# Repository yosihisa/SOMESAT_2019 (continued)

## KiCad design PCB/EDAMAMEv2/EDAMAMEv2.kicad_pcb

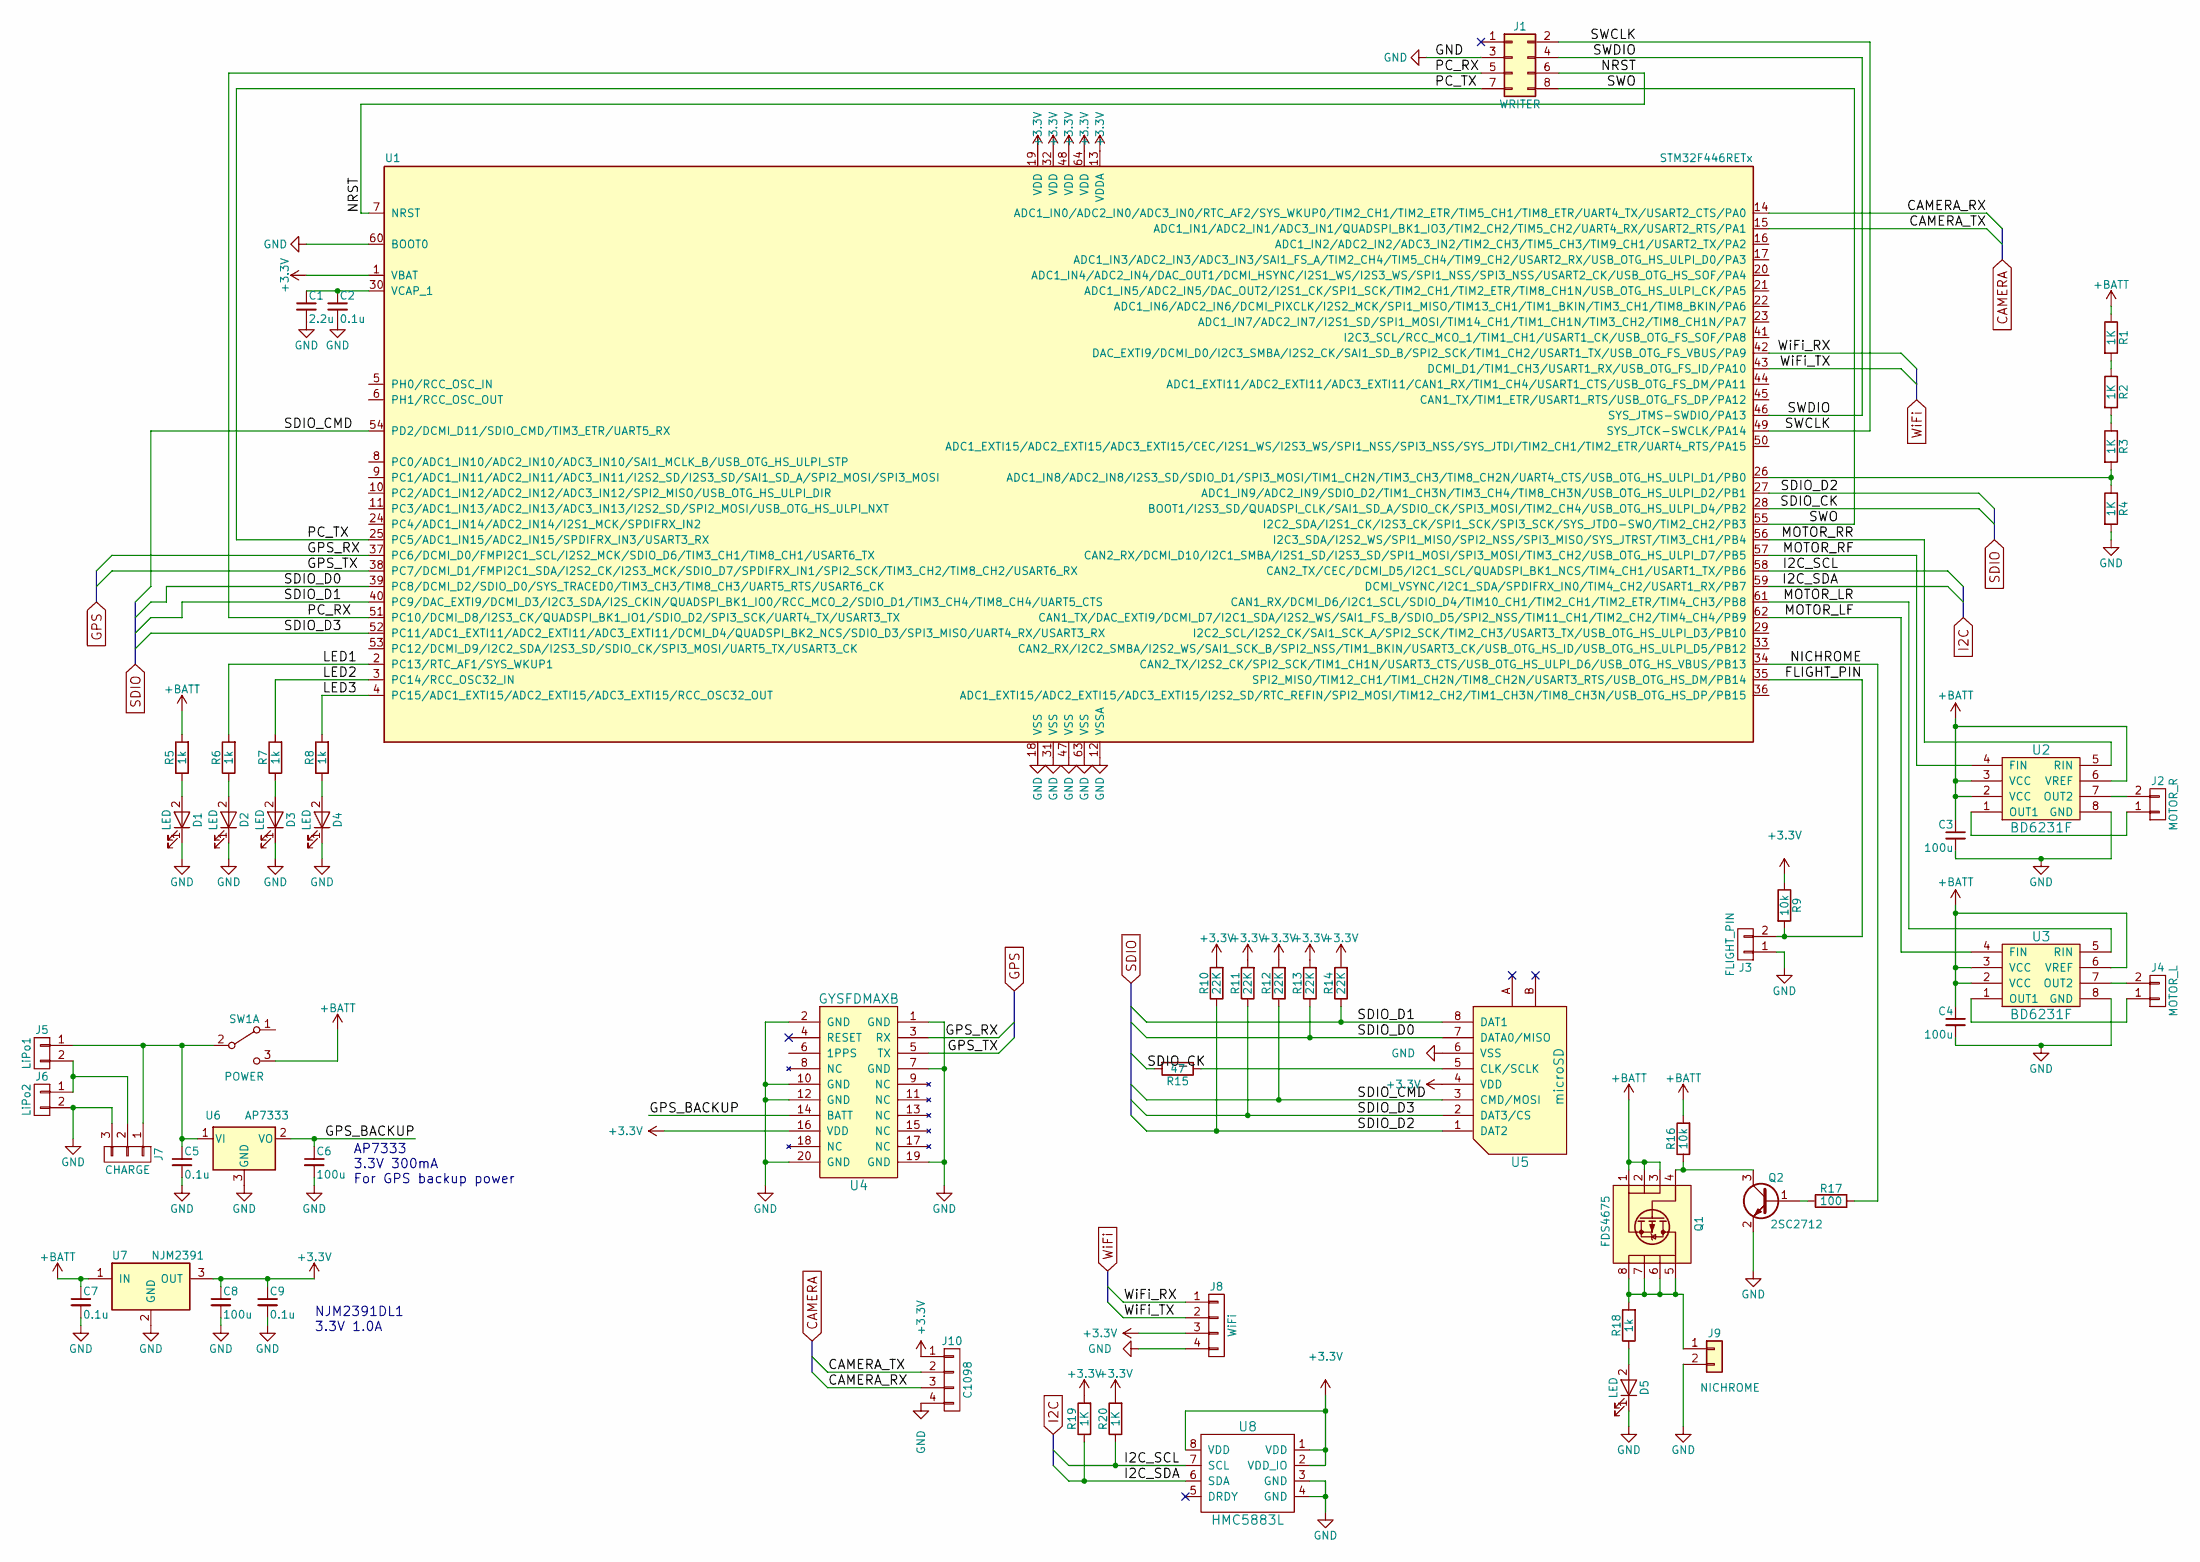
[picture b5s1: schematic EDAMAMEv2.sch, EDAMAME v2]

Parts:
C1: 2.2u; C_0603_HandSoldering
C2, C5, C7, C9: 0.1u; C_0603_HandSoldering
C3, C4: 100u; C_1210_HandSoldering
C6, C8: 100u; C_1206_HandSoldering
D1, D2, D3, D4, D5: LED; LED_0603
J1: WRITER; Pin_Header_Straight_2x04_Pitch2.54mm
J2: MOTOR_R; B2B-EH
J3: FLIGHT_PIN; Pin_Header_Angled_1x02_Pitch2.54mm
J4: MOTOR_L; B2B-EH
J5: LiPo1; S2B-EH
J6: LiPo2; S2B-EH
J7: CHARGE; B3B-EH
J8: WiFi; ZUNDA_WIRELESS
J9: NICHROME; TerminalBlock_bornier-2_P5.08mm
J10: C1098; Pin_Header_Straight_1x04_Pitch2.00mm
Q1: FDS4675; SOIC-8_3.9x4.9mm_Pitch1.27mm
Q2: 2SC2712; SOT-23_Handsoldering
R1, R2, R3, R4, R19, R20: 1K; R_0603_HandSoldering
R5, R6, R7, R8, R18: 1k; R_0603_HandSoldering
R9, R16: 10k; R_0603_HandSoldering
R10, R11, R12, R13, R14: 22K; R_0603_HandSoldering
R15: 47; R_0603_HandSoldering
R17: 100; R_0603_HandSoldering
SW1: POWER; SS-12D01-VG4
U1: STM32F446RETx; LQFP-64_10x10mm_Pitch0.5mm
U2, U3: BD6231F; SOIC-8_3.9x4.9mm_Pitch1.27mm
U4: GYSFDMAXB
U5: microSD
U6: AP7333; SOT-23
U7: NJM2391; TO-252-2_Rectifier
U8: HMC5883L; DIP-8_W7.62mm

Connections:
+3V3: C8.1, C9.1, J8.3, J10.1, R9.1, R10.2, R11.2, R12.2, R13.2, R14.2, R19.2, R20.2, U1.1 (VBAT), U1.13 (VDDA), U1.19 (VDD), U1.32 (VDD), U1.48 (VDD), U1.64 (VDD), U4.16 (VDD), U5.4 (VDD), U7.3 (OUT), U8.1 (VDD), U8.2 (VDD_IO), U8.8 (VDD)
+BATT: C3.1, C4.1, C7.1, Q1.1 (D), Q1.2 (G), Q1.3 (S), R1.1, R5.2, R16.2, SW1.3 (C), U2.2 (VCC), U2.3 (VCC), U2.6 (VREF), U3.2 (VCC), U3.3 (VCC), U3.6 (VREF), U7.1 (IN)
/CAMERA_RX: J10.3, U1.14 (ADC1_IN0/ADC2_IN0/ADC3_IN0/RTC_AF2/SYS_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)
/CAMERA_TX: J10.2, U1.15 (ADC1_IN1/ADC2_IN1/ADC3_IN1/QUADSPI_BK1_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)
/FLIGHT_PIN: J3.2, R9.2, U1.35 (SPI2_MISO/TIM12_CH1/TIM1_CH2N/TIM8_CH2N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)
/GPS_BACKUP: C6.1, U4.14 (BATT), U6.2 (VO)
/GPS_RX: U1.37 (PC6/DCMI_D0/FMPI2C1_SCL/I2S2_MCK/SDIO_D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), U4.3 (RX)
/GPS_TX: U1.38 (PC7/DCMI_D1/FMPI2C1_SDA/I2S2_CK/I2S3_MC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), U4.5 (TX)
/I2C_SCL: R20.1, U1.58 (CAN2_TX/CEC/DCMI_D5/I2C1_SCL/QUADSPI_BK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), U8.7 (SCL)
/I2C_SDA: R19.1, U1.59 (DCMI_VSYNC/I2C1_SDA/SPDIFRX_IN0/TIM4_CH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), U8.6 (SDA)
/LED1: R6.2, U1.2 (PC13/RTC_AF1/SYS_WKUP1)
/LED2: R7.2, U1.3 (PC14/RCC_OSC32_IN)
/LED3: R8.2, U1.4 (PC15/ADC1_EXTI15/ADC2_EXTI15/ADC3_EXTI1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)
/MOTOR_LF: U1.62 (CAN1_TX/DAC_EXTI9/DCMI_D7/I2C1_SDA/I2S2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), U3.4 (FIN)
/MOTOR_LR: U1.61 (CAN1_RX/DCMI_D6/I2C1_SCL/SDIO_D4/TIM10_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), U3.5 (RIN)
/MOTOR_RF: U1.57 (CAN2_RX/DCMI_D10/I2C1_SMBA/I2S1_SD/I2S3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), U2.4 (FIN)
/MOTOR_RR: U1.56 (I2C3_SDA/I2S2_WS/SPI1_MISO/SPI2_NSS/SPI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), U2.5 (RIN)
/NICHROME: R17.2, U1.34 (CAN2_TX/I2S2_CK/SPI2_SCK/TIM1_CH1N/USAR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)
/NRST: J1.6, U1.7 (NRST)
/PC_RX: J1.5, U1.51 (PC10/DCMI_D8/I2S3_CK/QUADSPI_BK1_IO1/SD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)
/PC_TX: J1.7, U1.25 (PC5/ADC1_IN15/ADC2_IN15/SPDIFRX_IN3/USA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)
/SDIO_CK: R15.2, U1.28 (BOOT1/I2S3_SD/QUADSPI_CLK/SAI1_SD_A/SDI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)
/SDIO_CMD: R12.1, U1.54 (PD2/DCMI_D11/SDIO_CMD/TIM3_ETR/UART5_RX), U5.3 (CMD/MOSI)
/SDIO_D0: R13.1, U1.39 (PC8/DCMI_D2/SDIO_D0/SYS_TRACED0/TIM3_CH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), U5.7 (DATA0/MISO)
/SDIO_D1: R14.1, U1.40 (PC9/DAC_EXTI9/DCMI_D3/I2C3_SDA/I2S_CKIN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), U5.8 (DAT1)
/SDIO_D2: R10.1, U1.27 (ADC1_IN9/ADC2_IN9/SDIO_D2/TIM1_CH3N/TIM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), U5.1 (DAT2)
/SDIO_D3: R11.1, U1.52 (PC11/ADC1_EXTI11/ADC2_EXTI11/ADC3_EXTI1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), U5.2 (DAT3/CS)
/SWCLK: J1.2, U1.49 (SYS_JTCK-SWCLK/PA14)
/SWDIO: J1.4, U1.46 (SYS_JTMS-SWDIO/PA13)
/SWO: J1.8, U1.55 (I2C2_SDA/I2S1_CK/I2S3_CK/SPI1_SCK/SPI3_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)
/WiFi_RX: J8.1, U1.42 (DAC_EXTI9/DCMI_D0/I2C3_SMBA/I2S2_CK/SAI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)
/WiFi_TX: J8.2, U1.43 (DCMI_D1/TIM1_CH3/USART1_RX/USB_OTG_FS_I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)
GND: C1.2, C2.2, C3.2, C4.2, C5.2, C6.2, C7.2, C8.2, C9.2, D1.1 (K), D2.1 (K), D3.1 (K), D4.1 (K), D5.1 (K), J1.3, J3.1, J6.2, J7.3, J8.4, J9.2, J10.4, Q2.2 (E), R4.2, U1.12 (VSSA), U1.18 (VSS), U1.31 (VSS), U1.47 (VSS), U1.60 (BOOT0), U1.63 (VSS), U2.8 (GND), U3.8 (GND), U4.1 (GND), U4.2 (GND), U4.7 (GND), U4.10 (GND), U4.12 (GND), U4.19 (GND), U4.20 (GND), U5.6 (VSS), U6.3 (GND), U7.2 (GND), U8.3 (GND), U8.4 (GND)
unnamed: C1.1, C2.1, U1.30 (VCAP_1)
unnamed: C5.1, J5.1, J7.1, SW1.2 (B), U6.1 (VI)
unnamed: D1.2 (A), R5.1
unnamed: D2.2 (A), R6.1
unnamed: D3.2 (A), R7.1
unnamed: D4.2 (A), R8.1
unnamed: D5.2 (A), R18.1
unnamed: J2.1, U2.1 (OUT1)
unnamed: J2.2, U2.7 (OUT2)
unnamed: J4.1, U3.1 (OUT1)
unnamed: J4.2, U3.7 (OUT2)
unnamed: J5.2, J6.1, J7.2
unnamed: J9.1, Q1.5, Q1.6, Q1.7, Q1.8, R18.2
unnamed: Q1.4, Q2.3 (C), R16.1
unnamed: Q2.1 (B), R17.1
unnamed: R1.2, R2.1
unnamed: R2.2, R3.1
unnamed: R3.2, R4.1, U1.26 (ADC1_IN8/ADC2_IN8/I2S3_SD/SDIO_D1/SPI3_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)
unnamed: R15.1, U5.5 (CLK/SCLK)

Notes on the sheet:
NJM2391DL1 3.3V 1.0A
AP7333 3.3V 300mA For GPS backup power

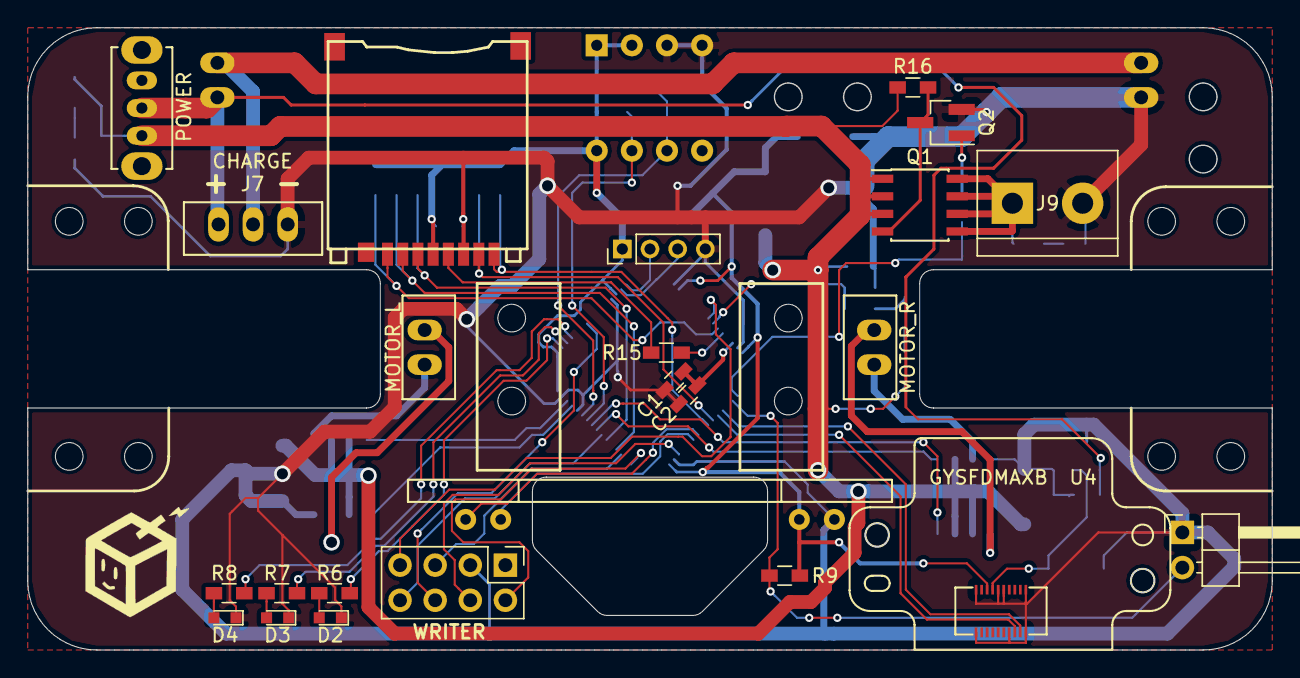
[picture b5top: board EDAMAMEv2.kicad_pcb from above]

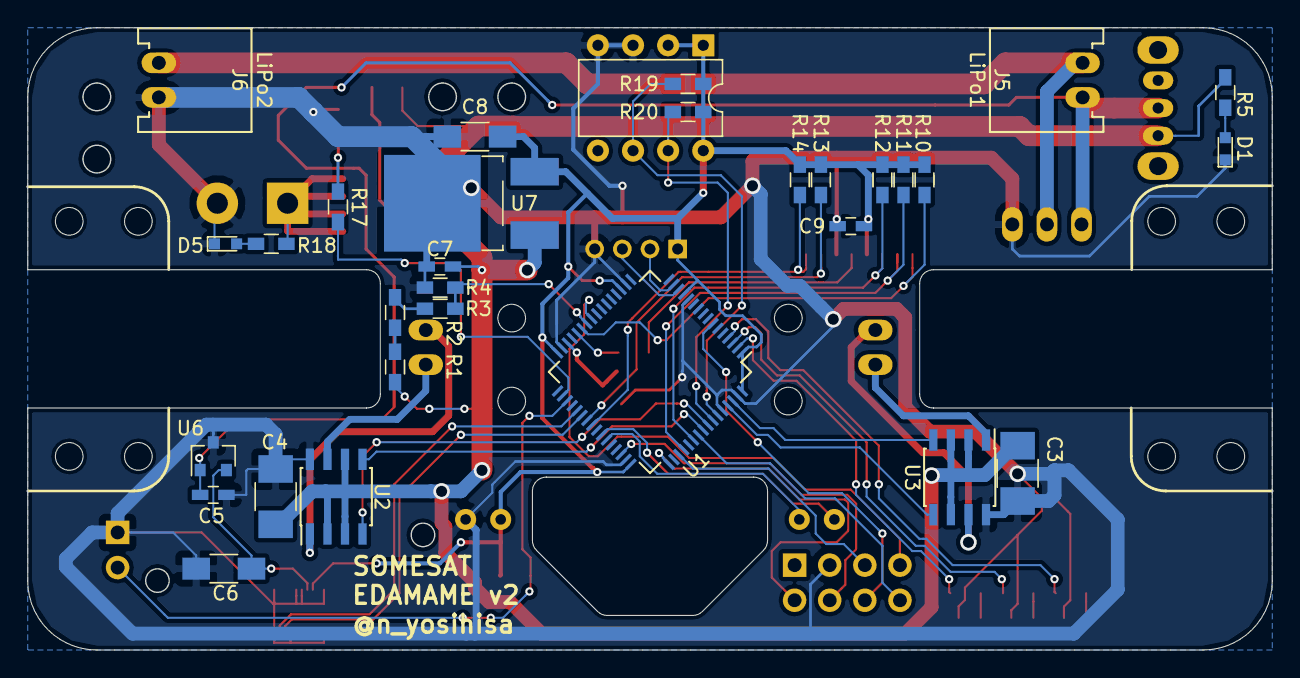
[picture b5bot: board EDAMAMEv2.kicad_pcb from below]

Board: 2 copper layers, 90.0 x 45.0 mm, 55 parts (32 on the bottom side), 52 nets.

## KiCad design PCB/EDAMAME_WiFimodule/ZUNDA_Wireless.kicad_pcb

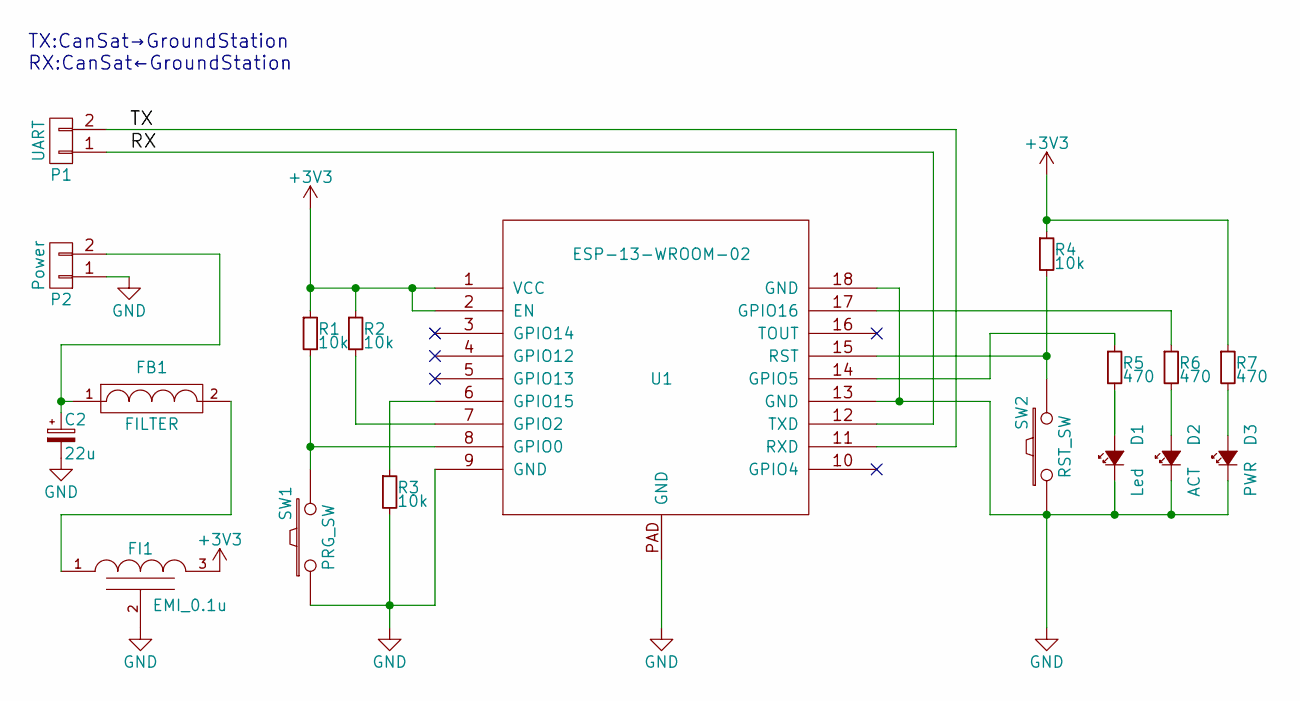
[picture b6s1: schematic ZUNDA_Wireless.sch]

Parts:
C2: 22u; CP_Tantalum_Case-B_EIA-3528-21_Reflow
D1: Led; 1608
D2: ACT; 1608
D3: PWR; 1608
FB1: FILTER; 1608
FI1: EMI_0.1u; EMI_Filter2012
P1: UART; Pin_Header_Angled_1x02_Pitch2.54mm
P2: Power; Pin_Header_Angled_1x02_Pitch2.54mm
R1, R2, R3, R4: 10k; 1608
R5, R6, R7: 470; 1608
SW1: PRG_SW; SKRPACE010_kai
SW2: RST_SW; SKRPACE010_kai
U1: ESP-13-WROOM-02

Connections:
+3V3: FI1.3 (VO), R1.1, R2.1, R4.1, R7.1, U1.1 (VCC), U1.2 (EN)
/RX: P1.1, U1.12 (TXD)
/TX: P1.2, U1.11 (RXD)
GND: C2.2, D1.1 (K), D2.1 (K), D3.1 (K), FI1.2 (GND), P2.1, R3.2, SW1.1, SW2.1, U1.9 (GND), U1.13 (GND), U1.18 (GND), U1.PAD (GND)
unnamed: C2.1, FB1.1, P2.2
unnamed: D1.2 (A), R5.2
unnamed: D2.2 (A), R6.2
unnamed: D3.2 (A), R7.2
unnamed: FB1.2, FI1.1 (VI)
unnamed: R1.2, SW1.2, U1.8 (GPIO0)
unnamed: R2.2, U1.7 (GPIO2)
unnamed: R3.1, U1.6 (GPIO15)
unnamed: R4.2, SW2.2, U1.15 (RST)
unnamed: R5.1, U1.14 (GPIO5)
unnamed: R6.1, U1.17 (GPIO16)

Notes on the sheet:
TX:CanSat→GroundStation RX:CanSat←GroundStation

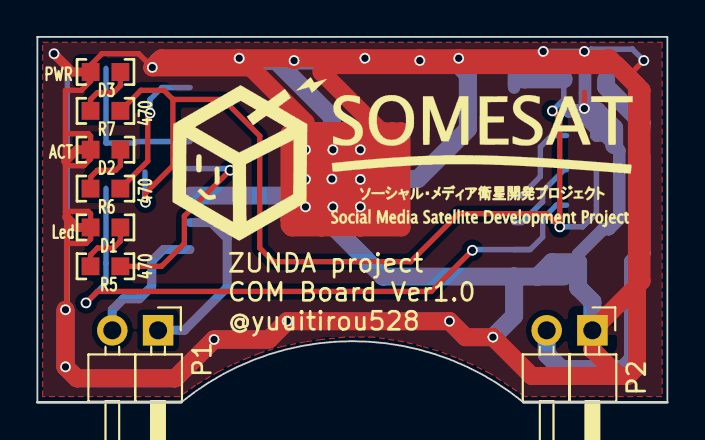
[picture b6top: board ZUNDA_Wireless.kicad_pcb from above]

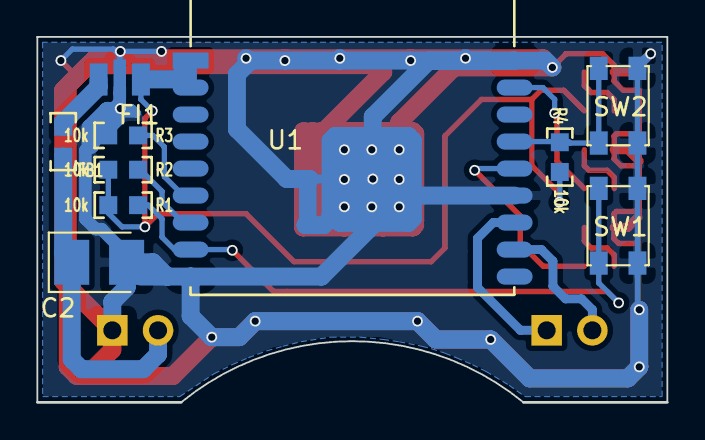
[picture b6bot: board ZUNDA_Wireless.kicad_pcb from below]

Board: 2 copper layers, 35.0 x 20.3 mm, 18 parts (10 on the bottom side), 15 nets.

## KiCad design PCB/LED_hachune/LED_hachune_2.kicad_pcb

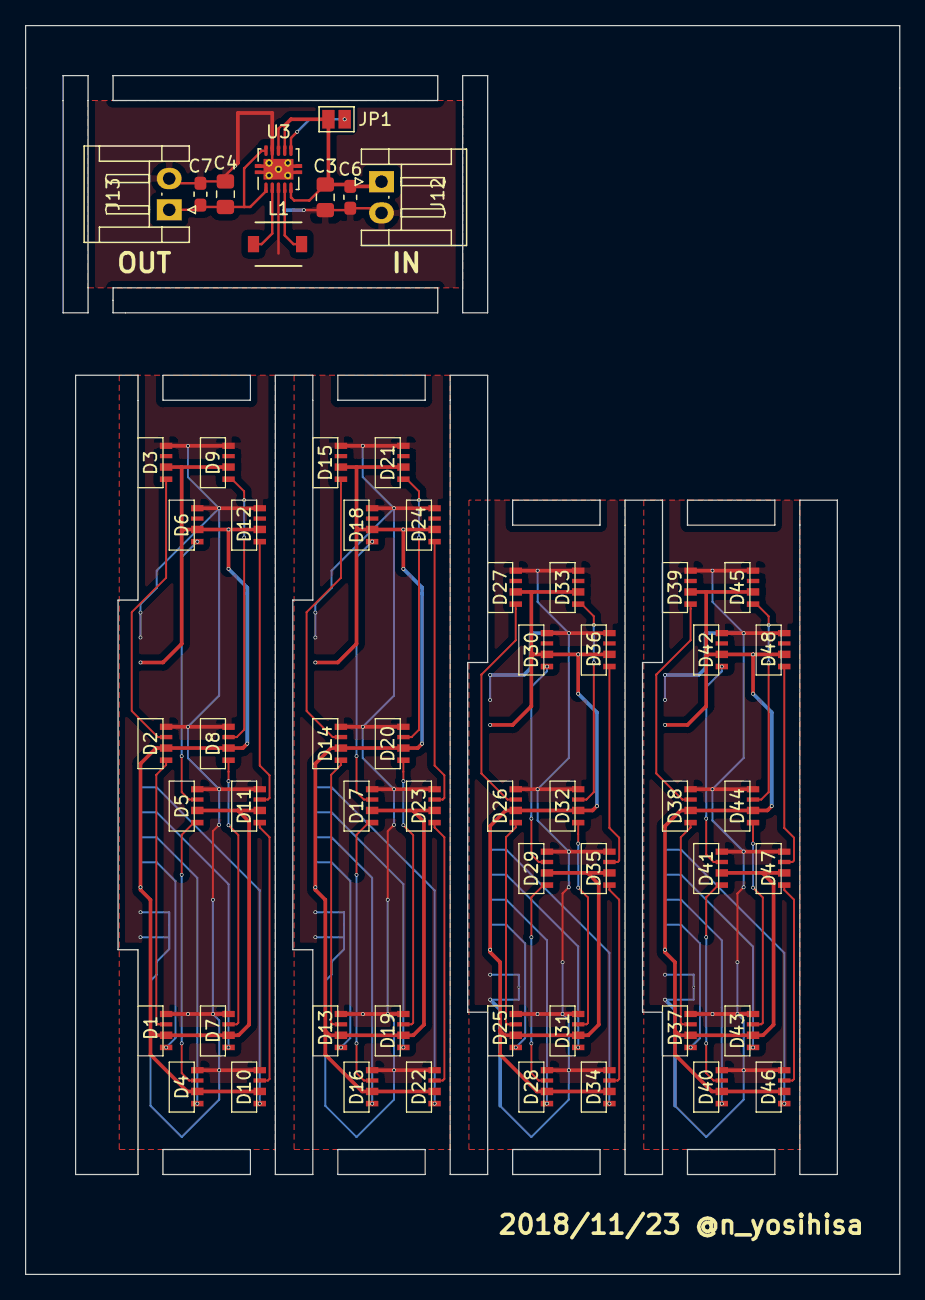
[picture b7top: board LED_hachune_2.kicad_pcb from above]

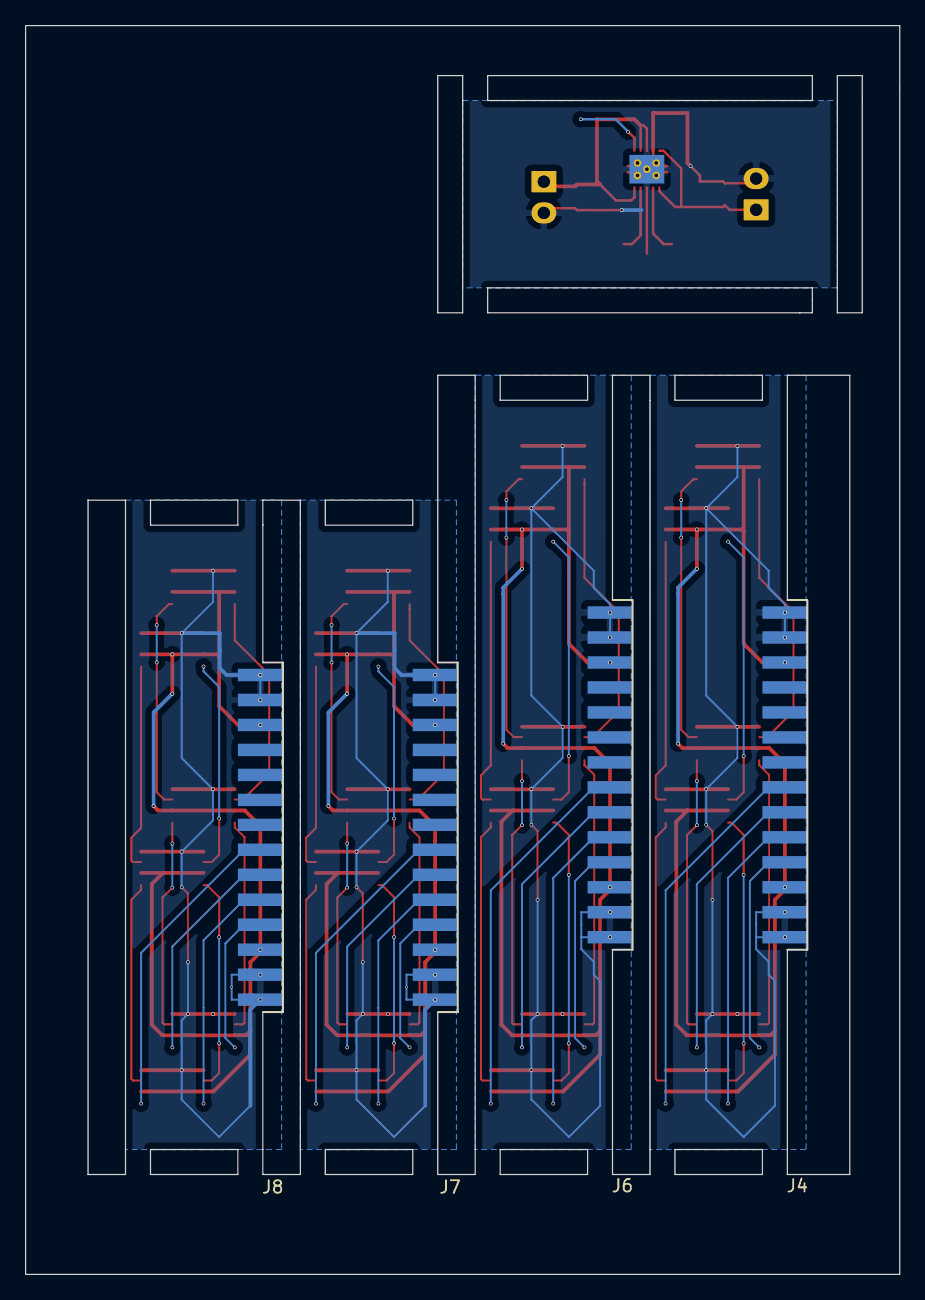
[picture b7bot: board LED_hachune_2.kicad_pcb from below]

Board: 2 copper layers, 70.0 x 100.0 mm, 61 parts (4 on the bottom side), 62 nets.

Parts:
C3, C4: 10u; C_0805_2012Metric_Pad1.15x1.40mm_HandSolder
C6, C7: 0.1u; C_0603_1608Metric_Pad1.05x0.95mm_HandSolder
D1, D2, D3, D4, D5, D6, D7, D8, D9, D10, D11, D12, D13, D14, D15, D16, D17, D18, D19, D20, D21, D22, D23, D24, D25, D26, D27, D28, D29, D30, D31, D32, D33, D34, D35, D36, D37, D38, D39, D40, D41, D42, D43, D44, D45, D46, D47, D48: S6812Side; S6812Side_top
J4, J6, J7, J8: LED_L; LED_Frame
J12: IN; JST_EH_S02B-EH_1x02_P2.50mm_Horizontal
J13: OUT; JST_EH_S02B-EH_1x02_P2.50mm_Horizontal
JP1: EN; SolderJumper-2_P1.3mm_Open_Pad1.0x1.5mm
L1: 2.2uH VLF4012-2R2; inductor_VLF4012-2R2
U3: TPS63001; Texas_S-PVSON-N10_ThermalVias

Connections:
GNDD: C3.2, C4.2, C6.2, C7.2, J12.2, J13.2, U3.3, U3.9, U3.11
unnamed: C3.1, C6.1, J12.1, JP1.1, U3.5, U3.7, U3.8
unnamed: C4.1, C7.1, J13.1, U3.1, U3.10
unnamed: D1.1, J4.4
unnamed: D1.2, D2.2, D3.2, D4.2, D5.2, D6.2, D7.2, D8.2, D9.2, D10.2, D11.2, D12.2, J4.3, J4.12
unnamed: D1.3, D2.1
unnamed: D1.4, D2.4, D3.4, D4.4, D5.4, D6.4, D7.4, D8.4, D9.4, D10.4, D11.4, D12.4, J4.1, J4.2, J4.13, J4.14
unnamed: D2.3, D3.1
unnamed: D4.1, J4.5
unnamed: D4.3, D5.1
unnamed: D5.3, D6.1
unnamed: D7.1, J4.6
unnamed: D7.3, D8.1
unnamed: D8.3, D9.1
unnamed: D10.1, J4.7
unnamed: D10.3, D11.1
unnamed: D11.3, D12.1
unnamed: D13.1, J6.4
unnamed: D13.2, D14.2, D15.2, D16.2, D17.2, D18.2, D19.2, D20.2, D21.2, D22.2, D23.2, D24.2, J6.3, J6.12
unnamed: D13.3, D14.1
unnamed: D13.4, D14.4, D15.4, D16.4, D17.4, D18.4, D19.4, D20.4, D21.4, D22.4, D23.4, D24.4, J6.1, J6.2, J6.13, J6.14
unnamed: D14.3, D15.1
unnamed: D16.1, J6.5
unnamed: D16.3, D17.1
unnamed: D17.3, D18.1
unnamed: D19.1, J6.6
unnamed: D19.3, D20.1
unnamed: D20.3, D21.1
unnamed: D22.1, J6.7
unnamed: D22.3, D23.1
unnamed: D23.3, D24.1
unnamed: D25.1, J7.4
unnamed: D25.2, D26.2, D27.2, D28.2, D29.2, D30.2, D31.2, D32.2, D33.2, D34.2, D35.2, D36.2, J7.3, J7.12
unnamed: D25.3, D26.1
unnamed: D25.4, D26.4, D27.4, D28.4, D29.4, D30.4, D31.4, D32.4, D33.4, D34.4, D35.4, D36.4, J7.1, J7.2, J7.13, J7.14
unnamed: D26.3, D27.1
unnamed: D28.1, J7.5
unnamed: D28.3, D29.1
unnamed: D29.3, D30.1
unnamed: D31.1, J7.6
unnamed: D31.3, D32.1
unnamed: D32.3, D33.1
unnamed: D34.1, J7.7
unnamed: D34.3, D35.1
unnamed: D35.3, D36.1
unnamed: D37.1, J8.4
unnamed: D37.2, D38.2, D39.2, D40.2, D41.2, D42.2, D43.2, D44.2, D45.2, D46.2, D47.2, D48.2, J8.3, J8.12
unnamed: D37.3, D38.1
unnamed: D37.4, D38.4, D39.4, D40.4, D41.4, D42.4, D43.4, D44.4, D45.4, D46.4, D47.4, D48.4, J8.1, J8.2, J8.13, J8.14
unnamed: D38.3, D39.1
unnamed: D40.1, J8.5
unnamed: D40.3, D41.1
unnamed: D41.3, D42.1
unnamed: D43.1, J8.6
unnamed: D43.3, D44.1
unnamed: D44.3, D45.1
unnamed: D46.1, J8.7
unnamed: D46.3, D47.1
unnamed: D47.3, D48.1
unnamed: JP1.2, U3.6
unnamed: L1.1, U3.4
unnamed: L1.2, U3.2

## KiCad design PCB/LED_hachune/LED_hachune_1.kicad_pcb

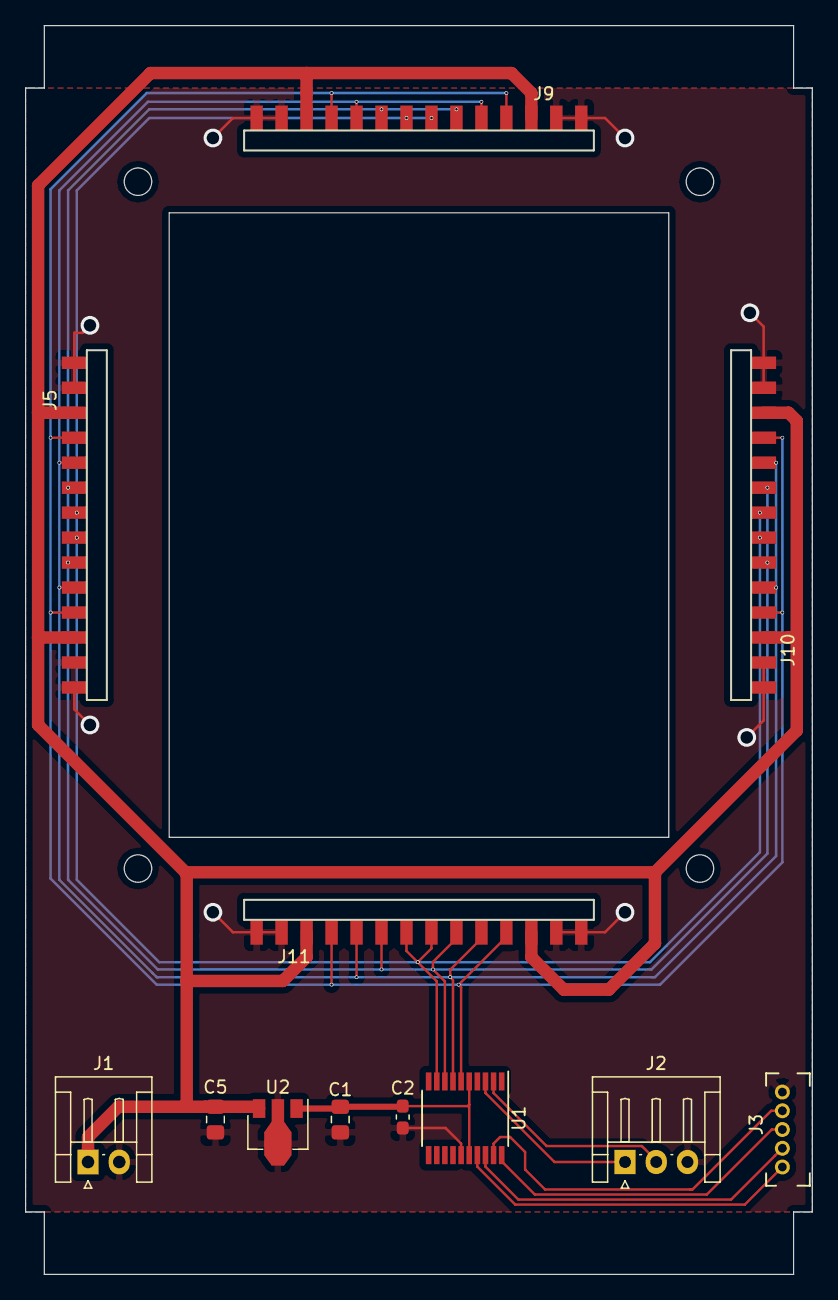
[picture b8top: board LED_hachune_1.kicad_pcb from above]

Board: 2 copper layers, 63.0 x 100.0 mm, 12 parts (0 on the bottom side), 13 nets.

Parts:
C1: 10u; C_0805_2012Metric_Pad1.15x1.40mm_HandSolder
C2: 0.1u; C_0603_1608Metric_Pad1.05x0.95mm_HandSolder
C5: 1u; C_0805_2012Metric_Pad1.15x1.40mm_HandSolder
J1: POWER; JST_EH_S02B-EH_1x02_P2.50mm_Horizontal
J2: DATA; JST_EH_S03B-EH_1x03_P2.50mm_Horizontal
J3: STlink
J5: LED_L; LED_socket
J9: LED_R; LED_socket
J10: LED_T; LED_socket
J11: LED_B; LED_socket
U1: STM32F042F6Px; TSSOP-20_4.4x6.5mm_P0.65mm
U2: XC6202P332PR-G; SOT-89-3

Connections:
+3V3: C1.1, C2.1, U1.5, U1.16, U2.1
+BATT: C5.1, J1.1, J5.3, J5.12, J9.3, J9.12, J10.3, J10.12, J11.3, J11.12, U2.3
/LED_0: J5.4, J5.11, J9.4, J9.11, J10.4, J10.11, J11.4, J11.11, U1.6
/LED_1: J5.5, J5.10, J9.5, J9.10, J10.5, J10.10, J11.5, J11.10, U1.7
/LED_2: J5.6, J5.9, J9.6, J9.9, J10.6, J10.9, J11.6, J11.9, U1.8
/LED_3: J5.7, J5.8, J9.7, J9.8, J10.7, J10.8, J11.7, J11.8, U1.9
/RX: J3.2, U1.18
/SCL: J2.1, U1.3
/SDA: J2.2, U1.2
/SWCLK: J3.3, U1.20
/SWDIO: J3.4, U1.19
/TX: J3.1, U1.17
GND: C1.2, C2.2, C5.2, J1.2, J2.3, J3.5, J5.1, J5.2, J5.13, J5.14, J9.1, J9.2, J9.13, J9.14, J10.1, J10.2, J10.13, J10.14, J11.1, J11.2, J11.13, J11.14, U1.15, U2.2

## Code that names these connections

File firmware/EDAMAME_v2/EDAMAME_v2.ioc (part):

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Mcu.Name=STM32F446R(C-E)Tx
Mcu.Package=LQFP64
Mcu.UserName=STM32F446RETx
PA0-WKUP.Mode=Asynchronous
PA0-WKUP.Signal=UART4_TX
PA1.Mode=Asynchronous
PA1.Signal=UART4_RX
PA10.GPIOParameters=GPIO_Label
PA10.GPIO_Label=WiFi
PA10.Mode=Asynchronous
PA10.Signal=USART1_RX
PA13.Mode=Serial_Wire
PA13.Signal=SYS_JTMS-SWDIO
PA14.Mode=Serial_Wire
PA14.Signal=SYS_JTCK-SWCLK
PA9.GPIOParameters=GPIO_Label
PA9.GPIO_Label=WiFi
PA9.Mode=Asynchronous
PA9.Signal=USART1_TX
PB0.Signal=ADCx_IN8
PB1.GPIOParameters=GPIO_PuPd
PB1.GPIO_PuPd=GPIO_NOPULL
PB1.Mode=SD_4_bits_Wide_bus
PB1.Signal=SDIO_D2
PB13.GPIOParameters=GPIO_Label
PB13.GPIO_Label=NICHROME
PB13.Signal=GPIO_Output
PB14.GPIOParameters=GPIO_Label
PB14.GPIO_Label=FLIGHT_PIN
PB14.Signal=GPIO_Input
PB2.GPIOParameters=GPIO_PuPd
PB2.GPIO_PuPd=GPIO_NOPULL
PB2.Mode=SD_4_bits_Wide_bus
PB2.Signal=SDIO_CK
PB3.Signal=SYS_JTDO-SWO
PB4.Signal=S_TIM3_CH1
PB5.Signal=S_TIM3_CH2
PB6.Mode=I2C
PB6.Signal=I2C1_SCL
PB7.Mode=I2C
PB7.Signal=I2C1_SDA
PB8.Signal=S_TIM2_CH1_ETR
PB9.Signal=S_TIM2_CH2
PC10.GPIOParameters=GPIO_Label
PC10.GPIO_Label=PC
PC10.Mode=Asynchronous
PC10.Signal=USART3_TX
PC11.GPIOParameters=GPIO_PuPd
PC11.GPIO_PuPd=GPIO_NOPULL
PC11.Mode=SD_4_bits_Wide_bus
PC11.Signal=SDIO_D3
PC13.GPIOParameters=GPIO_Label
PC13.GPIO_Label=LED1
PC13.Signal=GPIO_Output
PC14-OSC32_IN.GPIOParameters=GPIO_Label
PC14-OSC32_IN.GPIO_Label=LED2
PC14-OSC32_IN.Signal=GPIO_Output
PC15-OSC32_OUT.GPIOParameters=GPIO_Label
PC15-OSC32_OUT.GPIO_Label=LED3
PC15-OSC32_OUT.Signal=GPIO_Output
PC5.GPIOParameters=GPIO_Label
PC5.GPIO_Label=PC
PC5.Mode=Asynchronous
PC5.Signal=USART3_RX
PC6.GPIOParameters=GPIO_Label
PC6.GPIO_Label=GPS
PC6.Mode=Asynchronous
PC6.Signal=USART6_TX
PC7.GPIOParameters=GPIO_Label
PC7.GPIO_Label=GPS
PC7.Mode=Asynchronous
PC7.Signal=USART6_RX
PC8.GPIOParameters=GPIO_PuPd
PC8.GPIO_PuPd=GPIO_NOPULL
PC8.Mode=SD_4_bits_Wide_bus
PC8.Signal=SDIO_D0
PC9.GPIOParameters=GPIO_PuPd
PC9.GPIO_PuPd=GPIO_NOPULL
PC9.Mode=SD_4_bits_Wide_bus
PC9.Signal=SDIO_D1
PD2.GPIOParameters=GPIO_PuPd
PD2.GPIO_PuPd=GPIO_NOPULL
PD2.Mode=SD_4_bits_Wide_bus
PD2.Signal=SDIO_CMD
RCC.SYSCLKFreq_VALUE=180000000
RCC.SYSCLKSource=RCC_SYSCLKSOURCE_PLLCLK
board=EDAMAME

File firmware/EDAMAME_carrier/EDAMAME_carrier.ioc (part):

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Mcu.Name=STM32F042F6Px
Mcu.Package=TSSOP20
Mcu.UserName=STM32F042F6Px
PA0.GPIOParameters=GPIO_PuPd,GPIO_Label
PA0.GPIO_Label=Delay_4s
PA0.GPIO_PuPd=GPIO_PULLUP
PA0.Signal=GPIO_Input
PA1.GPIOParameters=GPIO_PuPd,GPIO_Label
PA1.GPIO_Label=Delay_2s
PA1.GPIO_PuPd=GPIO_PULLUP
PA1.Signal=GPIO_Input
PA10.GPIOParameters=GPIO_Label
PA10.GPIO_Label=B
PA10.Signal=GPIO_Output
PA13.Mode=Serial_Wire
PA13.Signal=SYS_SWDIO
PA14.Mode=Serial_Wire
PA14.Signal=SYS_SWCLK
PA2.GPIOParameters=GPIO_PuPd,GPIO_Label
PA2.GPIO_Label=Delay_1s
PA2.GPIO_PuPd=GPIO_PULLUP
PA2.Signal=GPIO_Input
PA3.GPIOParameters=GPIO_PuPd,GPIO_Label
PA3.GPIO_Label=Delay_0.5s
PA3.GPIO_PuPd=GPIO_PULLUP
PA3.Signal=GPIO_Input
PA4.GPIOParameters=GPIO_PuPd,GPIO_Label
PA4.GPIO_Label=Delay_0.25s
PA4.GPIO_PuPd=GPIO_PULLUP
PA4.Signal=GPIO_Input
PA5.GPIOParameters=GPIO_PuPd,GPIO_Label
PA5.GPIO_Label=Burn_0.5s
PA5.GPIO_PuPd=GPIO_PULLUP
PA5.Signal=GPIO_Input
PA6.GPIOParameters=GPIO_PuPd,GPIO_Label
PA6.GPIO_Label=Burn_1s
PA6.GPIO_PuPd=GPIO_PULLUP
PA6.Signal=GPIO_Input
PA7.GPIOParameters=GPIO_PuPd,GPIO_Label
PA7.GPIO_Label=Burn_2s
PA7.GPIO_PuPd=GPIO_PULLUP
PA7.Signal=GPIO_Input
PA9.GPIOParameters=GPIO_Label
PA9.GPIO_Label=A
PA9.Signal=GPIO_Output
PB1.Signal=S_TIM3_CH4
PB8.GPIOParameters=GPIO_PuPd,GPIO_Label
PB8.GPIO_Label=FlightPin
PB8.GPIO_PuPd=GPIO_PULLUP
PB8.Signal=GPIO_Input
PF0-OSC_IN.GPIOParameters=GPIO_PuPd,GPIO_Label
PF0-OSC_IN.GPIO_Label=Delay2_1
PF0-OSC_IN.GPIO_PuPd=GPIO_PULLUP
PF0-OSC_IN.Signal=GPIO_Input
PF1-OSC_OUT.GPIOParameters=GPIO_PuPd,GPIO_Label
PF1-OSC_OUT.GPIO_Label=Delay2_0.5
PF1-OSC_OUT.GPIO_PuPd=GPIO_PULLUP
PF1-OSC_OUT.Signal=GPIO_Input
RCC.SYSCLKFreq_VALUE=48000000
RCC.SYSCLKSource=RCC_SYSCLKSOURCE_HSI48
board=custom

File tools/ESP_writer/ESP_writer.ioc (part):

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Mcu.Name=STM32F446R(C-E)Tx
Mcu.Package=LQFP64
Mcu.UserName=STM32F446RETx
PA10.GPIOParameters=GPIO_PuPd,GPIO_Label
PA10.GPIO_Label=ESP_RX
PA10.GPIO_PuPd=GPIO_PULLUP
PA10.Signal=GPIO_Input
PA13.Mode=Serial_Wire
PA13.Signal=SYS_JTMS-SWDIO
PA14.Mode=Serial_Wire
PA14.Signal=SYS_JTCK-SWCLK
PA9.GPIOParameters=GPIO_Speed,GPIO_Label
PA9.GPIO_Label=ESP_TX
PA9.GPIO_Speed=GPIO_SPEED_FREQ_VERY_HIGH
PA9.Signal=GPIO_Output
PB4.Signal=GPIO_Output
PB5.Signal=GPIO_Output
PB8.Signal=GPIO_Output
PB9.Signal=GPIO_Output
PC10.GPIOParameters=GPIO_Speed,GPIO_Label
PC10.GPIO_Label=PC_TX
PC10.GPIO_Speed=GPIO_SPEED_FREQ_VERY_HIGH
PC10.Signal=GPIO_Output
PC5.GPIOParameters=GPIO_PuPd,GPIO_Label
PC5.GPIO_Label=PC_RX
PC5.GPIO_PuPd=GPIO_PULLUP
PC5.Signal=GPIO_Input
RCC.SYSCLKFreq_VALUE=180000000
RCC.SYSCLKSource=RCC_SYSCLKSOURCE_PLLCLK
board=EDAMAME

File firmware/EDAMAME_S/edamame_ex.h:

//えだまめS拡張ボード用クラスライブラリ
//将来的にedamame_func.inoはこのファイルに移行します。

#ifndef _edamame_ex_h
#define _edamame_ex_h

#include <Arduino.h>
#include <Wire.h>


#define INA226    0x45
#define MOTOR_LF  25
#define MOTOR_LR  26
#define MOTOR_RF  14
#define MOTOR_RR  27
#define NICHROME  13


//INA226と通信するクラス
class Power{
    public:
        Power(uint8_t);
        void update();
        void init();
        double voltage;
        double current;
    private:
        uint8_t address;
        int32_t v;
        int32_t a;
};

//モータ
class Motor{
    public:
        Motor(int ch0=0,int ch1=1,int ch2=2,int ch3=3);
        void init(int,int);
        void speed(int ,int);
    private:
        uint8_t ch[4];
        uint8_t pwm_bit;
        uint16_t pwm_hz;
};

//ニクロム線
class Nichrome{
    public:
        Nichrome(int ch=4);
        void fire(int);
    private:
        uint8_t pwm_ch;
};

#endif

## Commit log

2018-10-03 種コン2018
2018-10-03 NT金沢
2018-10-04 Readme
2018-10-05 Readme document 更新
2018-10-08 NT名古屋 ヘボコン RC化
2018-10-11 回路図追加
2018-10-12 ピンアサインシルクの修正
2018-10-12 Revert "ピンアサインシルクの修正"
    This reverts commit a283f1fcbc2505a9a6d1f3c0ea775a1104c0ca35.
2018-10-12 Revert "Revert "ピンアサインシルクの修正""
    This reverts commit 7053ee2e3a3dabeb02cb2a636f3767c6d3fc6b66.
2018-10-12 Readme更新 ブランチ分けテスト
2018-10-12 にゃーん
2018-10-22 I2Cが動かないんじゃ～～～～
2018-10-22 ESP32のライブラリは1.0.0-rc3を使ってくれ
2018-10-22 余計なもの削除
2018-10-23 edamame_func.inoからほとんどの関数をクラスライブラリに移行
2018-10-23 test_battery追加
2018-11-01 えだまめ3追加
2018-11-01 えだまめS readme更新
2018-11-01 readme 更新
2018-11-01 ドキュメントをwikiに移行
2018-11-05 わからんところまとめ第一弾
    正直お手上げ
2018-11-06 Lチカボード回路図追加
2018-11-06 回路変更(フットプリントの割り当てはまだ）
2018-11-07 フットプリント割当
2018-11-21 LEDはちゅね 基板製作途中
2018-11-22 LED_hacune レビュー1
2018-11-23 LED_hachune PCB NT加賀
2018-12-06 LED_hachune
2018-12-09 回路図AVRに変更
2018-12-16 点滅パターン変更
2018-12-18 AVR フットプリント・基板外形割当
2018-12-22 えだまめS 基板更新
2018-12-23 Add flightpin
2018-12-23 Add stl
2019-01-09 Add EDAMAME_S_M_PowerBoard schema
2019-01-19 Add carrier
2019-01-20 Add PCB layout
2019-01-20 Remove EDAMAMEv3
2019-01-20 move LED_Hachune
2019-02-07 fix edamame carrier
2019-02-13 Add LED
2019-02-20 EdamameS_V1.10
2019-02-20 Move repository(LED_hachune)
2019-02-20 EDAMAME_S v1.1(All) -> v1.2(sketch only)
2019-02-20 EDAMAME_S preE2E
2019-02-21 carrier
2019-02-21 move EDAMAME_S.ino
    https://gist.github.com/yosihisa/d14272492a6881c1af524f74480d74f5
2019-02-24 Add carrier firmware
2019-02-24 Add EDAMAME_S_M SRC
2019-02-25 Add GPS_log
2019-02-26 えだまめライブラリを更新
    UARTが動かん
    なんで？
2019-02-26 Revert "Add GPS_log"
    This reverts commit a7ef03d12424892d448dfa57f36a66670cb980ba.
2019-02-26 Revert "Revert "Add GPS_log""
    This reverts commit cc92bb86520bc498fab2962dba7d83d73cd6195b.
2019-02-26 Revert "えだまめライブラリを更新"
    This reverts commit 15bffdb8b9ba51e25b0d4683f290f2ecd6f6d2ca.
2019-02-26 V2→V2.1 本来のV2を復元
2019-02-27 画像認識なし えだまめS Rと同等
2019-02-27 制御周期の固定化 処理落ち対策
2019-02-28 画像認識追加
2019-03-02 Add tool
2019-03-02 Disabled WiFi
2019-03-02 Update Parameter
2019-03-07 ゴール座標,色更新 種コン本番β
